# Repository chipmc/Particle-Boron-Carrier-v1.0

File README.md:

View this project on [CADLAB.io](https://cadlab.io/project/1655).

# Particle-Boron-Carrier

This carrier is to support the use of the Boron in outdoor environments.

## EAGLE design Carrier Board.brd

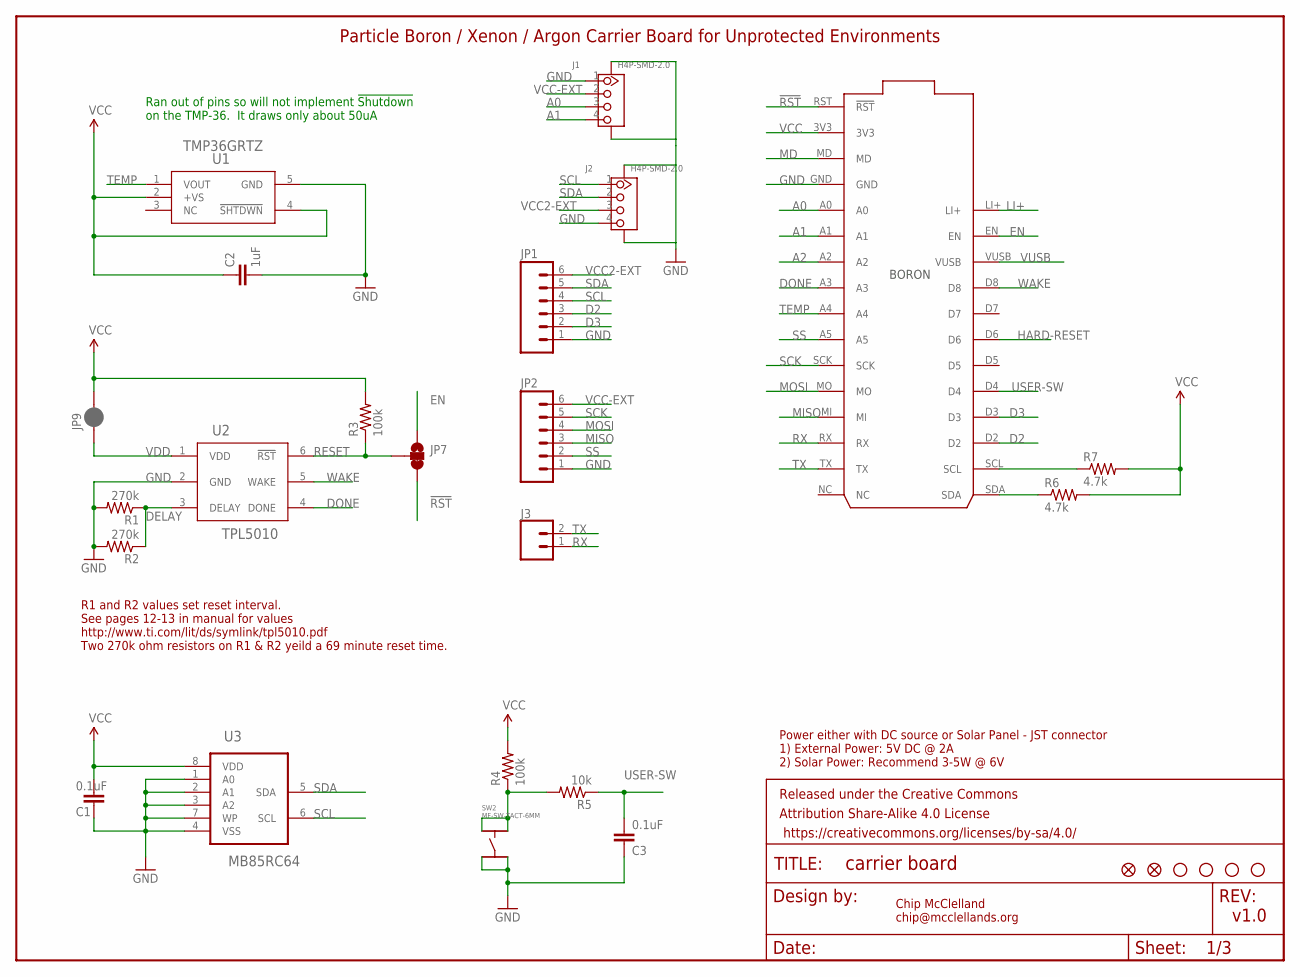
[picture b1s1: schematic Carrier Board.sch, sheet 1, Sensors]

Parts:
BORON/ARGON/XENON: PARTICLE-DEVICES-BORON; PARTICLE-DEVICES_BORON
C1, C3: 0.1uF; 0805@1
C2: 1uF; 0805@1
FD1, FD2: FIDUCIALUFIDUCIAL; FIDUCIAL-MICRO
FRAME1: FRAME-LETTER; CREATIVE_COMMONS
J1, J2: H4P-SMD-2.0; HW4-SMD-2.0
J3: CONN_02; 1X02
JP1, JP2: M06LOCK; 1X06_LOCK
JP3, JP4, JP5, JP6: STAND-OFF
JP7: JUMPER-SMT_3_1-NC_TRACE_SILK; SMT-JUMPER_3_1-NC_TRACE_SILK
JP9: JUMPER-SMT_2_NC_PASTE_SILK; SMT-JUMPER_2_NC_PASTE_SILK
R1, R2: 270k; 0805
R3, R4: 100k; 0805
R5: 10k; 0805
R6, R7: 4.7k; 0805
SW2: MF-SW-TACT-6MM; TACT6MM
U1: TMP36GRTZ; RJ_5
U2: TPL5010; TSOT-23
U3: MB85RC64; SOIC127P600X175-8N

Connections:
!RST: BORON/ARGON/XENON.RST (!RST), JP7.3
A0: BORON/ARGON/XENON.A0, J1.3
A1: BORON/ARGON/XENON.A1, J1.4
A2: BORON/ARGON/XENON.A2
D2: BORON/ARGON/XENON.D2, JP1.3; also elsewhere on the board
D3: BORON/ARGON/XENON.D3, JP1.2; also elsewhere on the board
DELAY: R1.1, R2.1, U2.3 (DELAY)
DONE: BORON/ARGON/XENON.A3, U2.4 (DONE)
EN: BORON/ARGON/XENON.EN, JP7.1; also elsewhere on the board
GND: BORON/ARGON/XENON.GND, C1.2, C2.2, C3.2, J1.1, J1.SS1, J1.SS2, J2.4, J2.SS1, J2.SS2, JP1.1, JP2.1, R1.2, R2.2, SW2.P$3, SW2.P$4, U1.5 (GND), U2.2 (GND), U3.1 (A0), U3.2 (A1), U3.3 (A2), U3.4 (VSS), U3.7 (WP); also elsewhere on the board
HARD-RESET: BORON/ARGON/XENON.D6; also elsewhere on the board
LI+: BORON/ARGON/XENON.LI+; also elsewhere on the board
MD: BORON/ARGON/XENON.MD
MISO: BORON/ARGON/XENON.MI, JP2.3
MOSI: BORON/ARGON/XENON.MO, JP2.4
unnamed: R4.1, R5.2, SW2.P$1, SW2.P$2
RESET: JP7.2, R3.1, U2.6 (!RST)
RX: BORON/ARGON/XENON.RX, J3.1
SCK: BORON/ARGON/XENON.SCK, JP2.5
SCL: BORON/ARGON/XENON.SCL, J2.1, JP1.4, R7.1, U3.6 (SCL); also elsewhere on the board
SDA: BORON/ARGON/XENON.SDA, J2.2, JP1.5, R6.1, U3.5 (SDA); also elsewhere on the board
SS: BORON/ARGON/XENON.A5, JP2.2
TEMP: BORON/ARGON/XENON.A4, U1.1 (VOUT)
TX: BORON/ARGON/XENON.TX, J3.2
USER-SW: BORON/ARGON/XENON.D4, C3.1, R5.1
VCC: BORON/ARGON/XENON.3V3, C1.1, C2.1, JP9.2, R3.2, R4.2, R6.2, R7.2, U1.2 (+VS), U1.4 (!SHTDWN), U3.8 (VDD); also elsewhere on the board
VCC2-EXT: J2.3, JP1.6; also elsewhere on the board
VCC-EXT: J1.2, JP2.6; also elsewhere on the board
VDD: JP9.1, U2.1 (VDD)
VUSB: BORON/ARGON/XENON.VUSB; also elsewhere on the board
WAKE: BORON/ARGON/XENON.D8, U2.5 (WAKE)

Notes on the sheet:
Chip McClelland chip@mcclellands.org
v1.0
Power either with DC source or Solar Panel - JST connector 1) External Power: 5V DC @ 2A 2) Solar Power: Recommend 3-5W @ 6V
Particle Boron / Xenon / Argon Carrier Board for Unprotected Environments
R1 and R2 values set reset interval. See pages 12-13 in manual for values http://www.ti.com/lit/ds/symlink/tpl5010.pdf Two 270k ohm resistors on R1 & R2 yeild a 69 minute reset time.
Ran out of pins so will not implement !Shutdown on the TMP-36. It draws only about 50uA

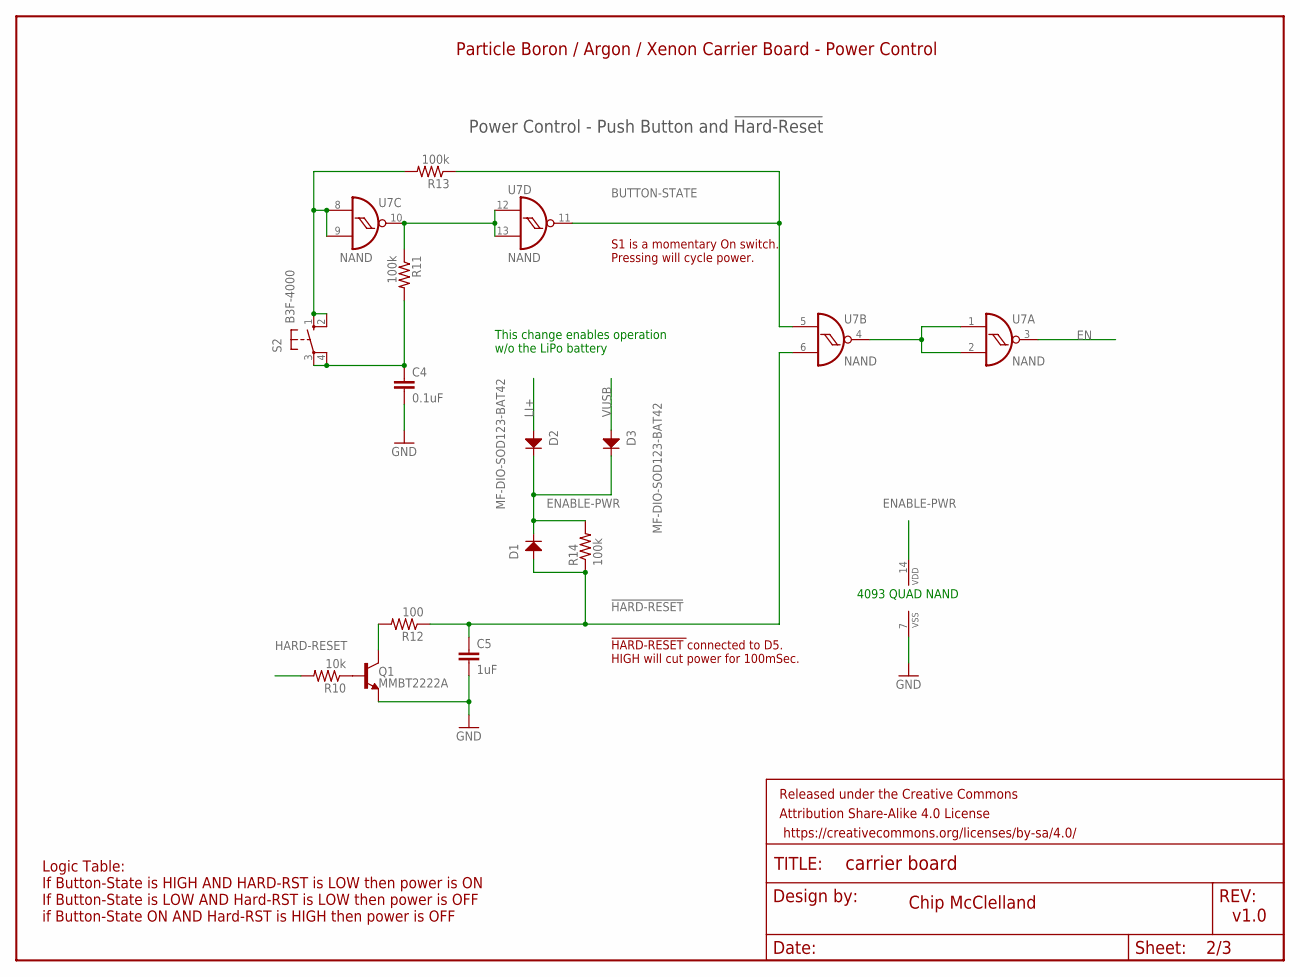
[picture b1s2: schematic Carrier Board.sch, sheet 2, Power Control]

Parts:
C4: 0.1uF; 0805@1
C5: 1uF; 0805@1
D1, D2, D3: MF-DIO-SOD123-BAT42; SOD-123
FRAME2: FRAME-LETTER; CREATIVE_COMMONS
Q1: MMBT2222A; SOT23-3
R10: 10k; 0805
R11, R13, R14: 100k; 0805
R12: 100; 0805
S2: B3F-4000; B3F-40XX-ROUND
U7: NAND; MC14093B-TSSOP14

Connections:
!HARD-RESET: C5.1, D1.ANODE, R12.1, R14.1, U7.6 (I1)
BUTTON-STATE: R13.1, U7.5 (I0), U7.11 (O)
EN: U7.3 (O); also elsewhere on the board
ENABLE-PWR: D1.CATHODE, D2.CATHODE, D3.CATHODE, R14.2, U7.14 (VDD)
GND: C4.2, C5.2, Q1.2 (E), U7.7 (VSS); also elsewhere on the board
HARD-RESET: R10.2; also elsewhere on the board
LI+: D2.ANODE; also elsewhere on the board
unnamed: U7.1 (I0), U7.2 (I1), U7.4 (O)
unnamed: R11.1, U7.10 (O), U7.12 (I0), U7.13 (I1)
unnamed: Q1.1 (B), R10.1
unnamed: Q1.3 (C), R12.2
unnamed: C4.1, R11.2, S2.3, S2.4 (P1)
unnamed: R13.2, S2.1 (S), S2.2 (S1), U7.8 (I0), U7.9 (I1)
VUSB: D3.ANODE; also elsewhere on the board

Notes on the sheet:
Particle Boron / Argon / Xenon Carrier Board - Power Control
4093 QUAD NAND
Power Control - Push Button and !Hard-Reset
Chip McClelland
v1.0
Logic Table: If Button-State is HIGH AND HARD-RST is LOW then power is ON If Button-State is LOW AND Hard-RST is LOW then power is OFF if Button-State ON AND Hard-RST is HIGH then power is OFF
!HARD-RESET !connected to D5. HIGH will cut power for 100mSec.
S1 is a momentary On switch. Pressing will cycle power.
This change enables operation w/o the LiPo battery

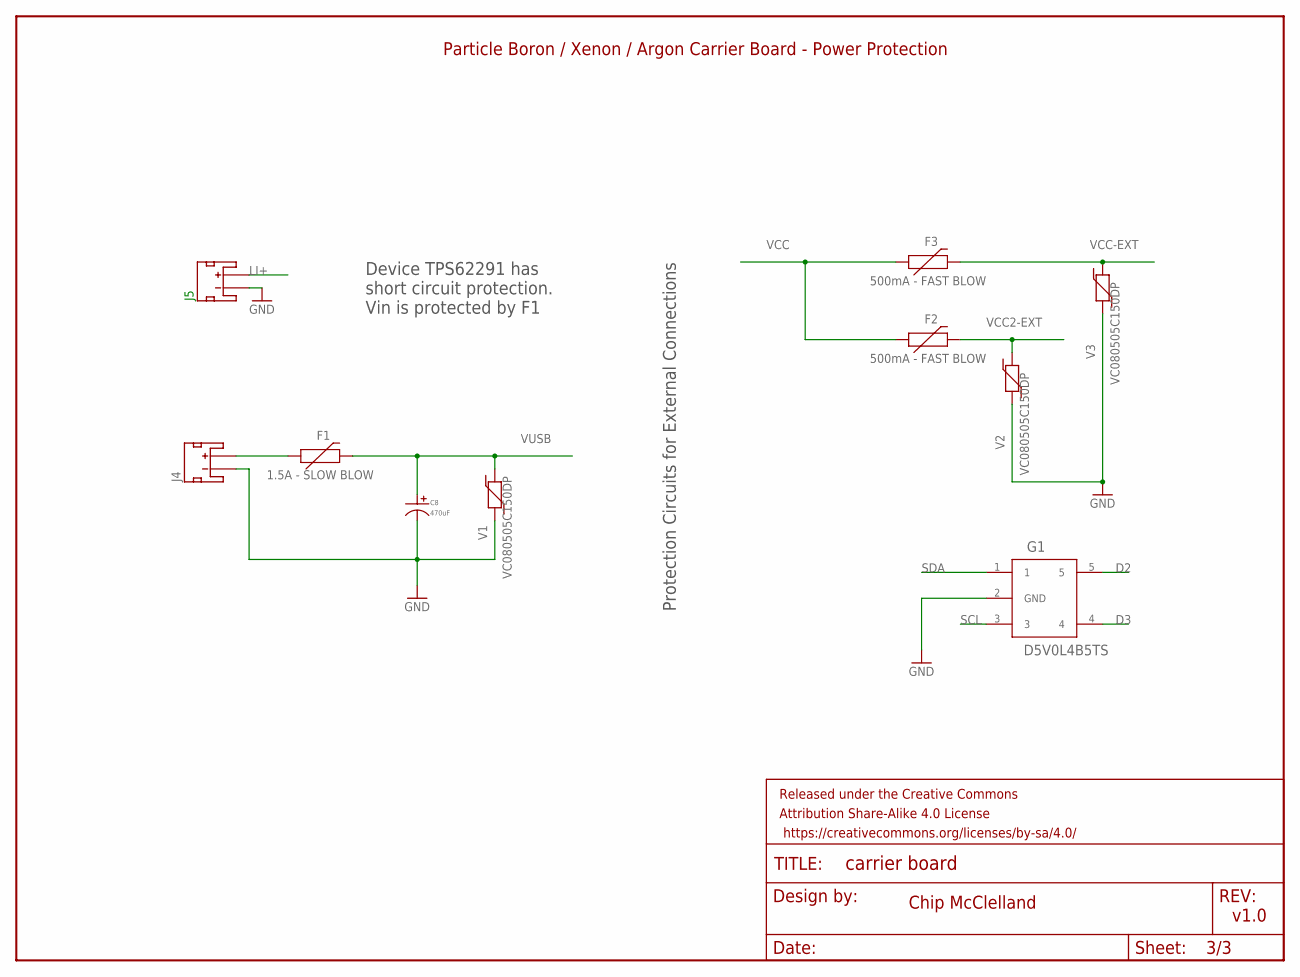
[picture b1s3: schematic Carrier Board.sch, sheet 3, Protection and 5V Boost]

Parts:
C8: 470uF; CP10MM
F1: 1.5A - SLOW BLOW; 1206
F2, F3: 500mA - FAST BLOW; 1206
FRAME3: FRAME-LETTER; CREATIVE_COMMONS
G1: D5V0L4B5TS; SOT-23-5
J4, J5: S2B-PH-SM4-TB(LF)(SN); JST-2-SMD
V1, V2, V3: VC080505C150DP; 0805

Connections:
D2: G1.5; also elsewhere on the board
D3: G1.4; also elsewhere on the board
DC-IN-EXT: F1.1, J4.2 (+)
GND: C8.P$2, G1.2 (GND), J4.1 (-), J5.1 (-), V1.1, V2.1, V3.1; also elsewhere on the board
LI+: J5.2 (+); also elsewhere on the board
SCL: G1.3; also elsewhere on the board
SDA: G1.1; also elsewhere on the board
VCC: F2.1, F3.1; also elsewhere on the board
VCC2-EXT: F2.2, V2.2; also elsewhere on the board
VCC-EXT: F3.2, V3.2; also elsewhere on the board
VUSB: C8.P$1, F1.2, V1.2; also elsewhere on the board

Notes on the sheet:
Protection Circuits for External Connections
Device TPS62291 has short circuit protection. Vin is protected by F1
Chip McClelland
v1.0
Particle Boron / Xenon / Argon Carrier Board - Power Protection

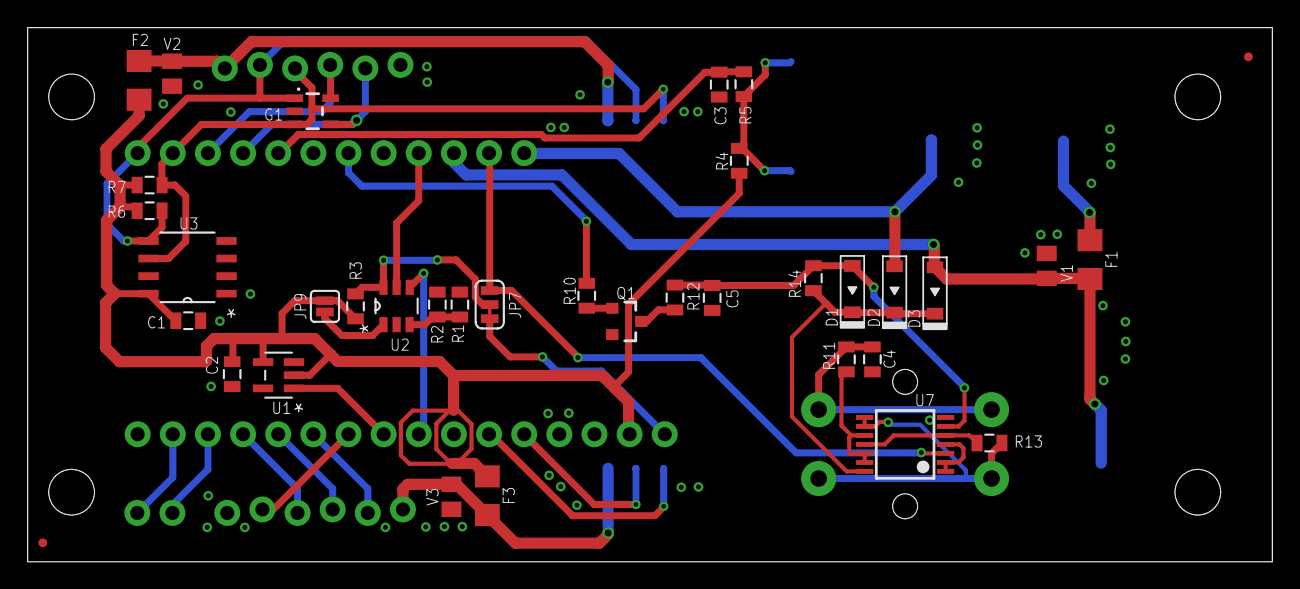
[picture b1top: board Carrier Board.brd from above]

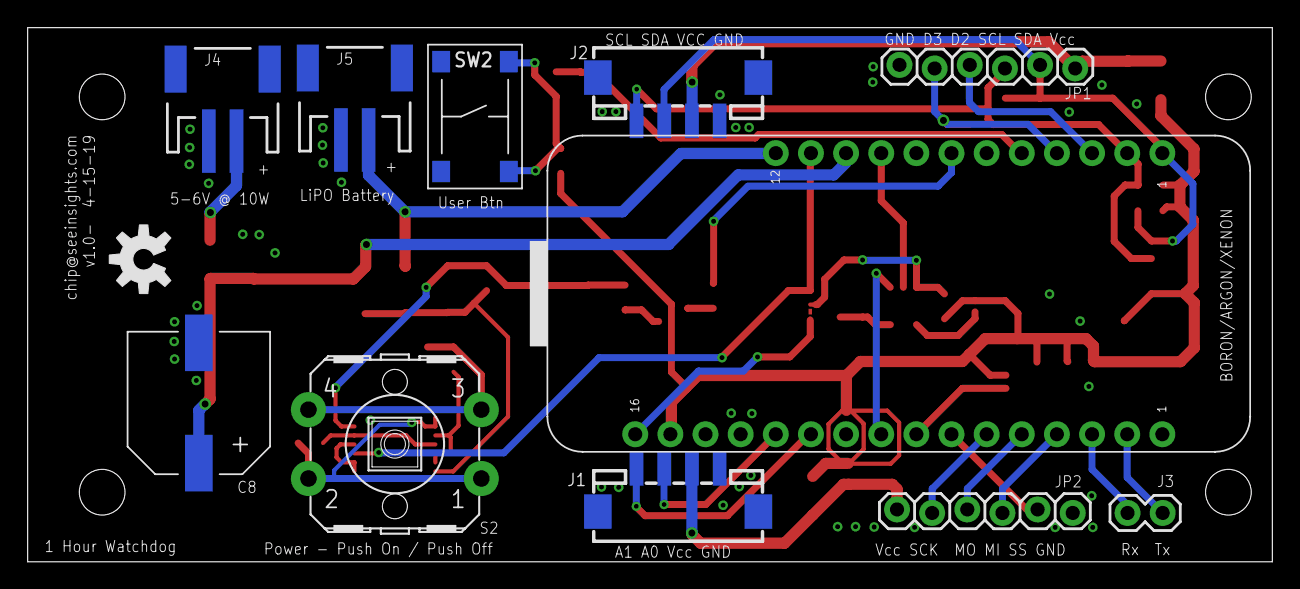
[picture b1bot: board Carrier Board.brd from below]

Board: 2 copper layers, 90.0 x 38.6 mm, 55 parts (12 on the bottom side), 39 nets.

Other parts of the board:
U$2: OSHW-LOGO-M

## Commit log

2019-03-28 Backlink to CADLAB.io has been added.
2019-03-28 v0.1 - First rough layout
    Just getting started.
2019-03-28 v0.1a - updated readme
2019-03-28 v0.11 - Refining placments
2019-03-28 More tweaks
    D8 for wake, no shutdown on TMP-36 and Hard-reset connected. Power protection for off-board VCC
2019-03-29 Added Heratch's v3 starter
2019-03-29 First Pass - Ready to send to OSHPark
2019-03-29 Labelling and less traces under the chips
2019-03-30 Got ride of traces under components
2019-04-13 Added 2-Grove Connectors
2019-04-15 v1.0 - sent to OSHPark today.
2019-04-15 v1.0 - minor tweaks post sending to OSHPark
2019-04-28 Had to move the Done pin to A3

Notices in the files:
parts and their libraries:
SparkFun-Aesthetics: Licensing: Creative Commons ShareAlike 4.0 International - https://creativecommons.org/licenses/by-sa/4.0
SparkFun-Aesthetics: Released under the Creative Commons Attribution Share-Alike 4.0 License
SparkFun-Aesthetics: https://creativecommons.org/licenses/by-sa/4.0
